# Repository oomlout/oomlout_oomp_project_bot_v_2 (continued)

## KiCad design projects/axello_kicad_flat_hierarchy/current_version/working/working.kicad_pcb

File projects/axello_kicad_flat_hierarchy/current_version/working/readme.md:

# kicad
 
## summary 
* id: axello_kicad_flat_hierarchy
* user: axello
* name: kicad
* board: flat_hierarchy
* repo: https://github.com/axello/kicad
* src_file_repo_kicad_pcb: demos/flat_hierarchy/flat_hierarchy.kicad_pcb
* src_file_repo_kicad_pcb_link: https://github.com/axello/kicad/tree/master/demos/flat_hierarchy/flat_hierarchy.kicad_pcb
* src_file_repo_kicad_sch: demos/flat_hierarchy/flat_hierarchy.kicad_sch
* src_file_repo_kicad_sch_link: https://github.com/axello/kicad/tree/master/demos/flat_hierarchy/flat_hierarchy.kicad_sch

* src_file_repo_sch: Arduino_Mega_433Mhz_Shield/Arduino_Mega.sch
* src_file_repo_sch_link: https://github.com/axello/kicad/tree/master/Arduino_Mega_433Mhz_Shield/Arduino_Mega.sch
* full details link: https://github.com/oomlout/oomlout_oomp_project_bot_v_2/tree/main/projects/axello_kicad_flat_hierarchy/current_version/working  

## pcb  

[board (pdf)](working.pdf)  

## working_bom
| Id | Designator | Footprint | Quantity | Designation | Supplier and ref |  | None | 
| --- | --- | --- | --- | --- | --- | --- | --- | 
| 1 | P3 | DIP-40_W15.24mm_Socket_LongPads | 1 | SUPP40 |  |  | [''] | 
| 2 | P2 | DIP-28_W7.62mm_Socket_LongPads | 1 | SUPP28 |  |  | [''] | 
| 3 | C1 | CP_Axial_L18.0mm_D6.5mm_P25.00mm_Horizontal | 1 | 100uF |  |  | [''] | 
| 4 | C2 | CP_Axial_L18.0mm_D6.5mm_P25.00mm_Horizontal | 1 | 220uF |  |  | [''] | 
| 5 | C3 | CP_Axial_L11.0mm_D6.0mm_P18.00mm_Horizontal | 1 | 22uF/25V |  |  | [''] | 
| 6 | C4 | C_Disc_D5.1mm_W3.2mm_P5.00mm | 1 | 0 |  |  | [''] | 
| 7 | C5 | C_Disc_D5.1mm_W3.2mm_P5.00mm | 1 | 10nF |  |  | [''] | 
| 8 | C6,C7,C8 | C_Disc_D5.1mm_W3.2mm_P5.00mm | 3 | 100nF |  |  | [''] | 
| 9 | C9 | C_Disc_D5.1mm_W3.2mm_P5.00mm | 1 | 22OnF |  |  | [''] | 
| 10 | D1 | D_DO-35_SOD27_P12.70mm_Horizontal | 1 | 1N4004 |  |  | [''] | 
| 11 | D2,D3,D4,D5,D6,D7,D11 | D_DO-35_SOD27_P7.62mm_Horizontal | 7 | BAT43 |  |  | [''] | 
| 12 | D8 | LED_D5.0mm | 1 | RED-LED |  |  | [''] | 
| 13 | D9 | LED_D5.0mm | 1 | GREEN-LED |  |  | [''] | 
| 14 | D10 | D_DO-35_SOD27_P12.70mm_Horizontal | 1 | SCHOTTKY |  |  | [''] | 
| 15 | D12 | LED_D5.0mm | 1 | YELLOW-LED |  |  | [''] | 
| 16 | J1 | DSUB-9_Female_Horizontal_P2.77x2.84mm_EdgePinOffset7.70mm_Housed_MountingHolesOffset9.12mm | 1 | DB9-FEMAL |  |  | [''] | 
| 17 | JP1 | PIN_ARRAY_2X1 | 1 | JUMPER |  |  | [''] | 
| 18 | L1 | INDUCTOR_V | 1 | 22uH |  |  | [''] | 
| 19 | P1 | Altech_AK300_1x02_P5.00mm_45-Degree | 1 | CONN_2 |  |  | [''] | 
| 20 | Q1 | TO-92 | 1 | BC237 |  |  | [''] | 
| 21 | Q2,Q3 | TO-92 | 2 | BC307 |  |  | [''] | 
| 22 | R2,R3,R4,R5,R6,R7,R1 | R_Axial_DIN0207_L6.3mm_D2.5mm_P10.16mm_Horizontal | 7 | 10K |  |  | [''] | 
| 23 | R8 | R_Axial_DIN0207_L6.3mm_D2.5mm_P10.16mm_Horizontal | 1 | 1K |  |  | [''] | 
| 24 | R9,R19,R20 | R_Axial_DIN0207_L6.3mm_D2.5mm_P10.16mm_Horizontal | 3 | 2.2K |  |  | [''] | 
| 25 | R10 | R_Axial_DIN0207_L6.3mm_D2.5mm_P10.16mm_Horizontal | 1 | 5.1K |  |  | [''] | 
| 26 | R11,R17 | R_Axial_DIN0207_L6.3mm_D2.5mm_P10.16mm_Horizontal | 2 | 22K |  |  | [''] | 
| 27 | R12,R13,R14,R21 | R_Axial_DIN0207_L6.3mm_D2.5mm_P10.16mm_Horizontal | 4 | 470 |  |  | [''] | 
| 28 | R15 | R_Axial_DIN0207_L6.3mm_D2.5mm_P10.16mm_Horizontal | 1 | 6.2K |  |  | [''] | 
| 29 | R18 | R_Axial_DIN0207_L6.3mm_D2.5mm_P10.16mm_Horizontal | 1 | 220 |  |  | [''] | 
| 30 | RV1 | RV2X4 | 1 | 1K |  |  | [''] | 
| 31 | U1 | DIP-8_W7.62mm_LongPads | 1 | 24Cxx |  |  | [''] | 
| 32 | U2 | DIP-14_W7.62mm_LongPads | 1 | 74HC125 |  |  | [''] | 
| 33 | U3 | TO-220-3_Horizontal_TabDown | 1 | 7805 |  |  | [''] | 
| 34 | U4 | DIP-8_W7.62mm_LongPads | 1 | LT1373 |  |  | [''] | 
| 35 | U5 | DIP-18_W7.62mm_Socket_LongPads | 1 | PIC_18_PINS |  |  | [''] | 
| 36 | U6 | DIP-8_W7.62mm_LongPads | 1 | PIC_8_PINS |  |  | [''] | 
| 37 | R16 | R_Axial_DIN0207_L6.3mm_D2.5mm_P10.16mm_Horizontal | 1 | 62K |  |  | [''] | 

## mounting_holes
| x | y | package | value | ref | size | 
| --- | --- | --- | --- | --- | --- | 
| 0.0 | 0.0 | DSUB-9_Female_Horizontal_P2.77x2.84mm_EdgePinOffset7.70mm_Housed_MountingHolesOffset9.12mm | DB9-FEMAL | J1 | m3 |

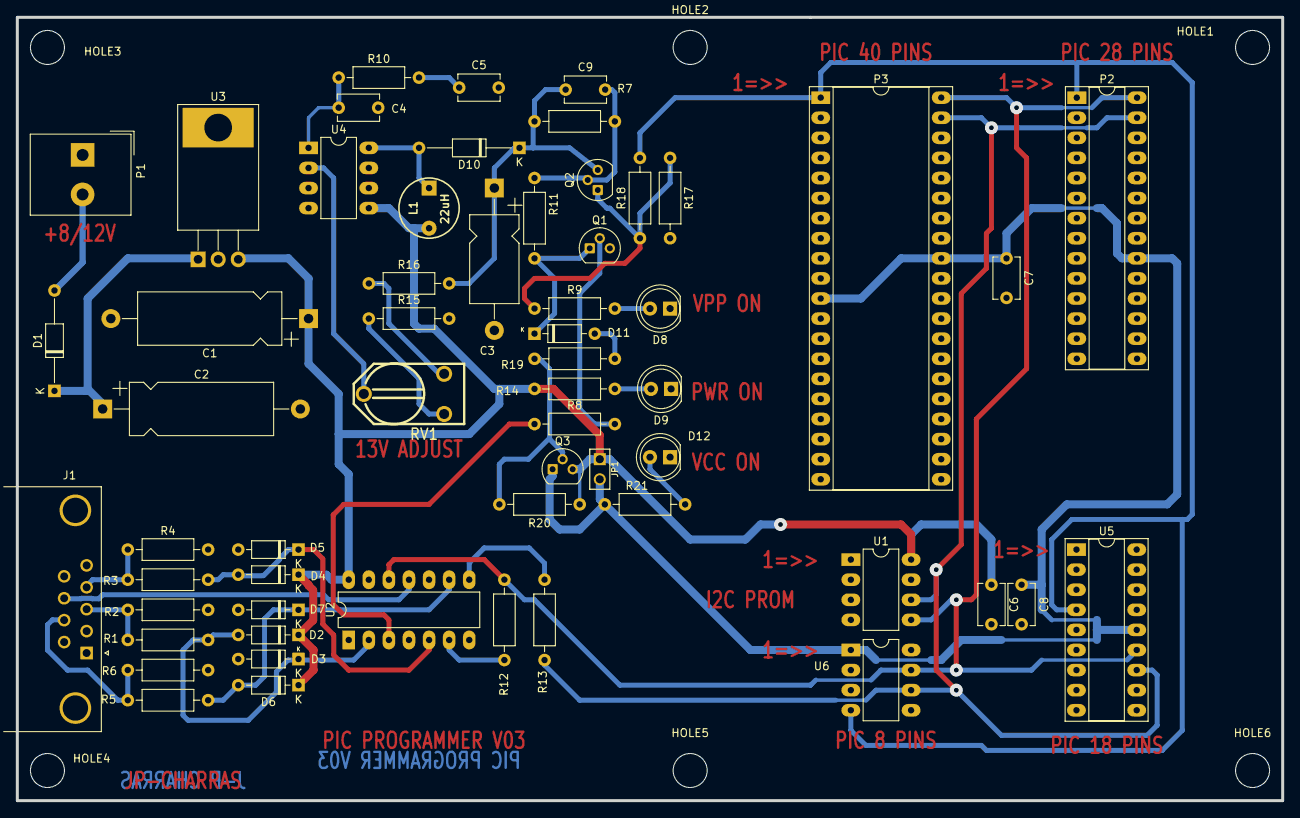
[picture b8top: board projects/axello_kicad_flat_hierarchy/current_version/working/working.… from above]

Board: 2 copper layers, 160.0 x 99.1 mm, 64 parts (0 on the bottom side), 34 nets.

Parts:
C1: 100uF; CP_Axial_L18.0mm_D6.5mm_P25.00mm_Horizontal
C2: 220uF; CP_Axial_L18.0mm_D6.5mm_P25.00mm_Horizontal
C3: 22uF/25V; CP_Axial_L11.0mm_D6.0mm_P18.00mm_Horizontal
C4: 0; C_Disc_D5.1mm_W3.2mm_P5.00mm
C5: 10nF; C_Disc_D5.1mm_W3.2mm_P5.00mm
C6, C7, C8: 100nF; C_Disc_D5.1mm_W3.2mm_P5.00mm
C9: 22OnF; C_Disc_D5.1mm_W3.2mm_P5.00mm
D1: 1N4004; D_DO-35_SOD27_P12.70mm_Horizontal
D2, D3, D4, D5, D6, D7, D11: BAT43; D_DO-35_SOD27_P7.62mm_Horizontal
D8: RED-LED; LED_D5.0mm
D9: GREEN-LED; LED_D5.0mm
D10: SCHOTTKY; D_DO-35_SOD27_P12.70mm_Horizontal
D12: YELLOW-LED; LED_D5.0mm
HOLE1, HOLE2, HOLE3, HOLE4, HOLE5, HOLE6: P***; MountingHole_4.3mm_M4_DIN965
J1: DB9-FEMAL; DSUB-9_Female_Horizontal_P2.77x2.84mm_EdgePinOffset7.70mm_H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
JP1: JUMPER; PIN_ARRAY_2X1
L1: 22uH; INDUCTOR_V
P1: CONN_2; Altech_AK300_1x02_P5.00mm_45-Degree
P2: SUPP28; DIP-28_W7.62mm_Socket_LongPads
P3: SUPP40; DIP-40_W15.24mm_Socket_LongPads
Q1: BC237; TO-92
Q2, Q3: BC307; TO-92
R1, R2, R3, R4, R5, R6, R7: 10K; R_Axial_DIN0207_L6.3mm_D2.5mm_P10.16mm_Horizontal
R8: 1K; R_Axial_DIN0207_L6.3mm_D2.5mm_P10.16mm_Horizontal
R9, R19, R20: 2.2K; R_Axial_DIN0207_L6.3mm_D2.5mm_P10.16mm_Horizontal
R10: 5.1K; R_Axial_DIN0207_L6.3mm_D2.5mm_P10.16mm_Horizontal
R11, R17: 22K; R_Axial_DIN0207_L6.3mm_D2.5mm_P10.16mm_Horizontal
R12, R13, R14, R21: 470; R_Axial_DIN0207_L6.3mm_D2.5mm_P10.16mm_Horizontal
R15: 6.2K; R_Axial_DIN0207_L6.3mm_D2.5mm_P10.16mm_Horizontal
R16: 62K; R_Axial_DIN0207_L6.3mm_D2.5mm_P10.16mm_Horizontal
R18: 220; R_Axial_DIN0207_L6.3mm_D2.5mm_P10.16mm_Horizontal
RV1: 1K; RV2X4
U1: 24Cxx; DIP-8_W7.62mm_LongPads
U2: 74HC125; DIP-14_W7.62mm_LongPads
U3: 7805; TO-220-3_Horizontal_TabDown
U4: LT1373; DIP-8_W7.62mm_LongPads
U5: PIC_18_PINS; DIP-18_W7.62mm_Socket_LongPads
U6: PIC_8_PINS; DIP-8_W7.62mm_LongPads

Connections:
/pic_programmer/PC-CLOCK-OUT: J1.7, R5.1, R6.1
/pic_programmer/PC-DATA-IN: J1.8, U2.11
/pic_programmer/PC-DATA-OUT: J1.4, R3.1, R4.1
/pic_programmer/VPP_ON: J1.3, R1.1, R2.1
CLOCK-RB6: P2.27, P3.39, R13.2, U1.6 (SCL), U5.12 (ICSPC/RB6), U6.6 (GP1)
DATA-RB7: P2.28, P3.40, R12.2, U1.5 (SDA), U2.12, U5.13 (ICSPD/RB7), U6.7 (GP0)
GND: C1.2, C2.2, C3.2, C4.2, C5.2, C6.2, C7.2, C8.2, D3.2 (A), D5.2 (A), D7.2 (A), D8.1 (K), D9.1 (K), D12.1 (K), J1.5, P1.1, P2.8, P2.19, P3.8, P3.12, P3.31, Q1.3 (E), R2.2, R4.2, R6.2, R15.2, R17.2, U1.1 (A0), U1.2 (A1), U1.3 (A2), U1.4 (GND), U2.1, U2.4, U2.7 (GND), U2.10, U2.13, U3.2 (GND), U4.6 (GND_S), U4.7 (GND), U5.5 (VSS), U6.8 (VSS)
unnamed: C2.1, D1.1 (K), U3.1 (VI)
unnamed: C4.1, R10.1, U4.1 (Vc)
unnamed: C5.1, R10.2
unnamed: C9.2, Q2.2 (B), R7.2, R11.2
unnamed: D1.2 (A), P1.2 (PM)
unnamed: D2.2 (A), D3.1 (K), R1.2, U2.2
unnamed: D4.2 (A), D5.1 (K), R3.2, U2.5
unnamed: D6.2 (A), D7.1 (K), R5.2, U2.9
unnamed: D8.2 (A), R9.2
unnamed: D9.2 (A), R14.2
unnamed: D10.2 (A), L1.1, U4.8 (Vsw)
unnamed: D11.1 (K), Q1.1 (C), R11.1
unnamed: D11.2 (A), R19.1
unnamed: D12.2 (A), R21.2
unnamed: Q1.2 (B), R8.2
unnamed: Q2.1 (C), R9.1, R17.1, R18.1
unnamed: Q3.2 (B), R19.2, R20.2
unnamed: R8.1, U2.3
unnamed: R12.1, U2.6
unnamed: R13.1, U2.8
unnamed: R15.1, RV1.1
unnamed: R16.1, RV1.3
unnamed: RV1.2, U4.2 (FB+)
VCC: C1.1, C6.1, D2.1 (K), D4.1 (K), D6.1 (K), JP1.1, L1.2, Q3.3 (E), R14.1, R20.1, U1.8 (VCC), U2.14 (VCC), U3.3 (VO), U4.5 (Vin)
VCC_PIC: C7.1, C8.1, JP1.2, P2.20, P3.11, P3.32, Q3.1 (C), R21.1, U5.14 (VDD), U6.1 (VDD)
VPP: C3.1, C9.1, D10.1 (K), Q2.3 (E), R7.1, R16.2
VPP-MCLR: P2.1, P3.1, R18.2, U5.4 (MCLR), U6.4 (GP3/MCLR)
